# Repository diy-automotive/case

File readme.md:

# DIY automotive Project

ある日、普段からCHIRIMENを触っているおっさんとか、あまり触ってなかったおっさんなどが集まり、レーザービーム付き車載システムを手作りすることになった。

というわけで、ここでは手作りしたハードについて書く。
機能とかシステム構成とかについては、[システム構成とかの資料](https://github.com/diy-automotive/codes) を読んでください。

**1号機**    

## 前提

ハード構成は下記条件で検討した。

- 車載を想定したシステムであるが具体的な車種は規定しない。いまのところ。たぶんセダンタイプでも大丈夫な感じで作ろう。ということになった
- ダッシュボード上の空間に(取り外し可能な形で)設置。(ずっと置くと車検が通らないなど)。というわけで、全体で 奥行き30cm以内 x 幅15cm以内 x 高さ 10cm以内 程度の大きさの箱（ケース）に収める感じにする
- 本体はダッシュボード上に（仮止めとはいえ）固定するため、モニターはある程度角度調整が可能な構造とする
- タッチパネルで操作したい。モニタは5インチくらいの大きさが良いだろうということになった
- 電源はシガーソケット (DC 12V)から取る。ただし車載せずともデモができないとおもしろくないので、家庭用コンセント(AC 100V)とシガーソケット(DC 12V)を変換する電源ユニットもつくる
- GPSちゃんと取れるのか？怪しいが、一旦はフロントガラス経由でGPS測位できる想定で作る。(GPSモジュールを本体とは離して置けないと困るので本体からケーブルで伸ばせるようにする)
- スピーカーとマイクを近づけるとハウリングするのでスピーカーとマイクを離して設置できる構造が必要。マイクを離す手もあったけど、マイクはUSBカメラと一体になってるのを使いたかったので、スピーカーを外付けすることにした。

## パーツ一覧 

というわけで、冒頭の写真の「１号機」で使ったパーツは下記の通り。

### A. そのまま使うパーツ

1. [Raspberry Pi 3 Model B](https://www.raspberrypi.org/products/raspberry-pi-3-model-b/) x 1
2. [5インチ タッチパネルモニタ](https://www.amazon.co.jp/ELECROW-%E3%83%87%E3%82%A3%E3%82%B9%E3%83%97%E3%83%AC%E3%82%A4-800x480%E8%A7%A3%E5%83%8F%E5%BA%A6-%E3%82%BF%E3%83%83%E3%83%81%E3%82%B9%E3%82%AF%E3%83%AA%E3%83%BC%E3%83%B3-Raspberry/dp/B013JECYF2) x 1
3. [Raspberry Pi カメラモジュール v1.3 (車の前方撮影カメラ用)](http://akizukidenshi.com/catalog/g/gM-10476/)
4. [ポータブルスピーカ JVC SP-A35M-S](https://www.amazon.co.jp/gp/product/B002VITVE0/ref=oh_aui_detailpage_o02_s00?ie=UTF8&psc=1) x 1
5. [USB GPSモジュール GT-730F/L(SiRF)](http://akizukidenshi.com/catalog/g/gM-09272/) x 1
6. [Raspberry Pi カメラ用延長ケーブル (20cm〜)](https://www.amazon.co.jp/gp/product/B00KDZBCD6/ref=oh_aui_detailpage_o01_s00?ie=UTF8&psc=1) x 1
7. [HDMI延長アダプタ (L字 180度回転)](https://www.amazon.co.jp/gp/product/B0721MJGNN/ref=oh_aui_detailpage_o02_s00?ie=UTF8&psc=1) x 1
8. [スリムHDMIケーブル](https://www.amazon.co.jp/gp/product/B00KPP3MPA/ref=oh_aui_detailpage_o08_s00?ie=UTF8&psc=1) x 1 
9. [赤色ドットレーザー](http://akizukidenshi.com/catalog/g/gM-11821/)
10. [シガープラグ電源ケーブル](https://www.amazon.co.jp/gp/product/B01KRFE63Y/ref=oh_aui_detailpage_o01_s00?ie=UTF8&psc=1) x 1
11. [RCサーボ ブラケットセット](https://robot.tsukumo.co.jp/products/detail/644) x 2
12. [L字型 3.5mmステレオオーディオジャック延長ケーブル (10cmくらい)](https://www.aliexpress.com/item/DC3-5mm-Male-to-Female-Extension-stereo-Audio-Cable-15cm-90-Degree-Angled/32262817004.html?spm=a2g0s.9042311.0.0.ZXPDmG)
13. [USB延長ケーブル (Type A)]()
14. [12V 5A ACアダプタ](http://akizukidenshi.com/catalog/g/gM-06961/)
15. [シガーソケット電源ケーブル](https://www.amazon.co.jp/%E3%82%B7%E3%82%AC%E3%83%BC%E3%82%BD%E3%82%B1%E3%83%83%E3%83%88-%E3%83%A1%E3%82%B9-12V%E7%94%A8-%E9%9B%BB%E6%BA%90%E3%82%B1%E3%83%BC%E3%83%96%E3%83%AB%E4%BB%98-30cm/dp/B078WPZV7Q/ref=sr_1_31?s=automotive&ie=UTF8&qid=1521952190&sr=1-31&keywords=%E9%9B%BB%E6%BA%90+%E3%82%B7%E3%82%AC%E3%83%BC%E3%82%BD%E3%82%B1%E3%83%83%E3%83%88)

 (※ 12. 13. を併せた[この製品](
https://www.amazon.co.jp/auto-AC-DC%E5%A4%89%E6%8F%9B%E3%82%A2%E3%83%80%E3%83%97%E3%82%BF%E3%83%BC12V-%E9%9B%BB%E6%BA%90%E5%A4%89%E6%8F%9B%E3%82%A2%E3%83%80%E3%83%97%E3%82%BF%E3%83%BC-%E3%82%B7%E3%82%AC%E3%83%BC%E3%82%BD%E3%82%B1%E3%83%83%E3%83%88%E3%82%BF%E3%82%A4%E3%83%97-HLT-1200500C/dp/B07116WZHF/ref=sr_1_28?s=automotive&ie=UTF8&qid=1521952061&sr=1-28&keywords=%E9%9B%BB%E6%BA%90+%E3%82%B7%E3%82%AC%E3%83%BC%E3%82%BD%E3%82%B1%E3%83%83%E3%83%88)でも良さそうだけど試してない)

### B. 改造して使うパーツ

1. [USBカメラ (F2Fカメラ用) iBuffalo BSWHD06M](https://www.amazon.co.jp/gp/product/B00GZAF89W/ref=oh_aui_detailpage_o02_s01?ie=UTF8&psc=1) x 1
2. Micro B USB電源ケーブル
3. USB Type Aコネクタが付いた USB2.0ケーブル

### C. 電子部品

1. [DCDCコンバータ](http://akizukidenshi.com/catalog/g/gK-07728/) x 1
2. [トグルスイッチ]()
3. コンデンサ 1000uF(35V) x 1、220uF(16V) x 2
4. LED x 2
5. 抵抗 1kΩ x 1 2kΩ x 1
6. ユニバーサル基板 x 2
7. 電線(5Aくらい流しても大丈夫そうな太いやつや、普通のジャンパーケーブル適量)
8. [Molex 1.25mmピッチコンタクト](https://www.sengoku.co.jp/mod/sgk_cart/detail.php?code=EEHD-4B5Z) 使うの5本だけど圧着難しくてミスるので x 10
9. [Molex 1.25mmピッチコネクタのハウジング (5P)](https://www.marutsu.co.jp/pc/i/41986/) x 2 (使うの1つだけど予備入れて)
10. [ADT7410温度センサー](http://akizukidenshi.com/catalog/g/gM-06675/) x 1
11. [Raspi用長足ピンソケット (2列x20)](http://akizukidenshi.com/catalog/g/gC-10702/) x 1
12. 分割ピンヘッダ(2.54mmピッチ) 1x40 x 1
13. [PCA9685 IC単体](https://jp.rs-online.com/web/p/led-display-drivers/7275649/)
14. チップ抵抗 (0805) 220Ω x 2 、10kΩ x 1
15. チップコンデンサ (0805) 10uF x 1
16. ゴムブッシュ(3mm径くらいのやつ) x 2

### D. ケース用パーツ

1. [金具 19Ω314-3 黒](https://www.amazon.co.jp/%E3%83%8F%E3%82%A4%E3%83%AD%E3%82%B8%E3%83%83%E3%82%AF-19%E3%82%AA%E3%83%A1%E3%82%AC314-3-%E3%82%B8%E3%83%A7%E3%82%A4%E3%83%B3%E3%83%88-19%CE%A9314-3-%E9%BB%92/dp/B00C39XL7K) x 2
2. [金具 BS-558](https://store.shopping.yahoo.co.jp/cocoatta/4903757115583.html?sc_e=slga_pla)
3. [金具 6005](https://store.shopping.yahoo.co.jp/ayahadio/4905034060050.html?sc_e=slga_pla)
4. [金具 6001](https://store.shopping.yahoo.co.jp/hands-net/4905034060012.html?sc_i=shp_pc_search_itemlist_shsr_title)

5. [アクリル版 (リンクにおいてあるdxfファイルでレーザーカットを依頼する)](https://github.com/diy-automotive/case)

### E. その他 (T.B.D.)

下記概要だけ記載しておく。※あとで詳細化する予定。

1. ネジ、スペーサー、ナット、ワッシャー等 (M2,M2.6,M3,M4) 適量
2. ジャンパーケーブル 適量
3. 電線適量。電源とかの工作に使う

## 制作に必要な工具

- 電動ドリル
- ドライバー
- はんだごて、はんだ吸い取り線、はんだ
- フラックス、フラックスクリーナー
- ラジオペンチ
- ニッパー
- カッター
- 圧着工具 ([PA-09](https://www.yodobashi.com/product/100000001002004022/)/[PA-20](https://www.yodobashi.com/product/100000001002493185/?gad1=&gad2=g&gad3=&gad4=56278881131&gad5=4733500117604394886&gad6=1o1&gclid=CjwKCAjw7tfVBRB0EiwAiSYGM2PXHVkw076M0nHblvUYxSvrJmiqklgOjumo8atqDQbhuTxs9HHcMBoCniEQAvD_BwE&xfr=pla))
- ワイヤーストリッパー

## 制作手順 

(T.B.D.) 写真いれる予定。。。

### 1. [アクリル板データ](./case/)のレーザーカットと修正

レーザーカットサービスにカットを依頼しておく。
リードタイムがかかるので、最低2週間前にはやっておく。
今回は、[elecrow Acrylic Laser Cutting Service](https://www.elecrow.com/5pcs-acrylic-laser-cutting-service.html)へ依頼。OCS使って1週間で届いた。

レーザーカットデータは残念ながら現時点(v1/v2両方) では不完全なので、`bottom.dxf`の1枚だけ（上部に利用する側のみ）ドリルで穴をあけておく。
 (将来v3以降で修正されるはずなので、この工程はなくなる予定) ※割れないよう慎重に行うこと

穴をあける箇所は特に指定はないが、下記 2箇所 (穴としては5穴) の穴あけを行う。

- トグルスイッチ固定用の穴 (6mmくらいの穴をあける。いきなりこれを開けようとすると割れるので2mmくらいの穴を広げた方が良い)
- サーボモータ固定用の穴 (サーボモータ固定用の穴はすでに空いているが、後ろ側に寄りすぎていて干渉するため、同じような 4隅 9mm 間隔 2mmの穴を　よりケースの端側に開ける )

### 2. [HAT](./hat/)の基板を製造

基板製造業者に投げておく。回しものではないが [elecrow](https://www.elecrow.com/pcb-manufacturing.html) にアクリル板と一緒に投げると一緒に送ってくれる。

### 3. 電源ユニットの制作

電源ユニットは、下記で構成される。AC電源側から記載する

1. ACアダプタ (加工の必要なし)
2. シガーソケット (電線の端にDCジャックを付けておく) ※基板で加工が必要
3. シガープラグ (電線の端をDCDCコンバータの入力側に接続。ターミナル経由なのでネジ止めだけ)
4. DCDCコンバータ (秋月のキットなので、そのまま作ればOK)
5. 分岐基板 (DCDCの出力側のターミナルにつなぐケーブルの先を2列のピンヘッダで分岐させる用の基板。DCDCの出力側のVCCラインにトグルスイッチを付けておく)

上記分岐基板につなぐのは、Raspiの電源と、サーボモータの電源だが両方ケーブルの改造が必要となる。

#### 3.1 Raspi電源用ケーブルの改造

市販のmicro B端子の付いたUSB充電ケーブルを切断、USB micro Bコネクタ側を残して切断した側をQIコネクタ(メス)に加工する

#### サーボモータの電源

これはHATの項に記載。

### 4. HATの制作とRaspiとの固定

[HAT](./hat/)のデータは今回用に設計したものではないので、いろいろそのままは使わない。
PCA9685関連の部分のみ作る感じで PCA9685と周辺のチップコンデンサ(10uF)、チップ抵抗(220Ω x 2, 10kΩ x 1)、サーボ接続用のピンヘッダ、RaspiのGPIO接続用の長足ピンソケットだけハンダ付け。電源はUSB経由ではなく表面のRaspiの電源付近にあるコンデンサ(220uF)の部分にコンデンサと一緒にケーブル（太めを付けないと燃える。燃えた）を直接はんだ付けし、ケーブル反対側を電源ユニットのジャンパーに刺せるようQIコネクタ（メス）に加工しておく。ケーブルの長さは10cm程度で良い。

HATが制作できたら、Raspiに固定する。
まず、Raspiにある4箇所の固定用穴の底面にM2.6mmのスペーサー（片方がネジになってる。ネジ側をRaspiの穴に挿す）と、上面に、両方がナットになってるスペーサーで挟み込んで止める。これを4箇所ともやっておく。

次に、HATをRaspiに重ね、HATの上からM2.6のネジで、下のスペーサーとHATを挟み込むような形でネジ止めしておく。

### 5. P2P通話用カメラの改造

USBカメラを分解し、基板部分のみ利用する。
基板の1.25mmピッチコネクタと反対側がUSB Type Aになったケーブルを別途制作する。安いUSBケーブルを切って端子を圧着して作る。
1.25mmピッチコネクタの圧着が難しいので注意。圧着工具PA-09を使う。

### 6. 前景撮影用カメラユニットの作成

サーボで動くカメラユニットを作成する。

`camera-parts-v2.dxf`を出力したアクリル板を使いRaspiカメラと小型レーザーを組み合わせたユニットを作る。
M2のスペーサーとネジを使って固定するが、`camera-parts-v2.dxf`の後面側のパーツは穴の間隔が合わないので、下の穴はスペーサーで終端にする。
レーザーはゴムブッシュでアクリル板に固定する。

次に、サーボブラケットセットを組み立てる。カメラとレーザーを組み合わせたユニットを最後にネジ止めする

カメラのリボンケーブルは、一番下側になるサーボブラケットの中を通すようにしておくとあとあと取り回しがしやすい。

### 7. モニター部分の制作

モニターとP2P通話用カメラをアクリルケースに固定する。
`back.dxf`を出力したアクリル板と、`front.dxf`を出力したアクリル板を使う。

1. M2のネジ・スペーサを使ってカメラを`front.dxf`を出力したアクリル板へ固定する

2. `back.dxf`を出力したアクリル板へ、[金具 6001](https://store.shopping.yahoo.co.jp/hands-net/4905034060012.html?sc_i=shp_pc_search_itemlist_shsr_title) をネジ止めする。モニターとの隙間に干渉しないよう、6mmくらいのネジ推奨。

3. モニターの背面に4箇所 M2のネジが出ているので、そこにM2のスペーサー (5mm) を4箇所止める。
4. `back.dxf`を出力したアクリル板とスペーサーをM2ネジで固定する。
5. 最後にカメラを固定した`front.dxf`を出力したアクリル板と、`back.dxf`を出力したアクリル板を M2 13mmのスペーサー経由でネジ止めして固定する

### 8. 本体部分の制作(底面から)

`bottom.dxf` 2枚で本体ケース部分を作る。2枚のうち1枚は、1. の工程で穴あけ加工済み。こちらは上面に使うので、ここでは加工していないもう１枚を使う。

1. アクリル板に、足となる [金具 19Ω314-3](https://www.amazon.co.jp/%E3%83%8F%E3%82%A4%E3%83%AD%E3%82%B8%E3%83%83%E3%82%AF-19%E3%82%AA%E3%83%A1%E3%82%AC314-3-%E3%82%B8%E3%83%A7%E3%82%A4%E3%83%B3%E3%83%88-19%CE%A9314-3-%E9%BB%92/dp/B00C39XL7K) のうち、Raspiの電源側に近い部分の方を先にネジ止めしておく。M4ネジを使い、アクリル板との間にはゴムワッシャーを入れておく。(振動対策)Raspiを重ねた後でネジが入れられなくなるため。あとで手で絞められるように蝶ナットを使う。
2. アクリル板に、4. でHATをつなげたRaspiをネジ止めする。Raspi側の底面にスペーサーが付いているので、アクリル板の反対側からネジ止めするだけで固定できるが、Raspiの電源側の角のネジだけは止めないでおく。下の足と干渉するため。
3. 次に電源ユニットをネジ止めする。間にスペーサーを入れた方がやりやすそうだがお好みで。
4. 5cmの M3スペーサーを、アクリル板の4角に付けておく。このスペーサーで上面との固定を行う。
5. 反対側の足(金具 19Ω314-3)もつけておく。こちら側もゴムワッシャー経由でアクリル版とネジで固定するが、(金具 19Ω314-3)の下に[金具 BS-558](https://store.shopping.yahoo.co.jp/cocoatta/4903757115583.html?sc_e=slga_pla) を挟んでから止めておく。金具 BS-558は、のちにモニターとの接続に使う。

### 9. 本体部分の制作(上面)

`bottom.dxf` 1. の工程で穴あけ加工済みの方のアクリル版を使い上面パネルを作る。
このパネルには、電源ユニットのトグルスイッチと、 前景撮影用カメラユニット(サーボモータブラケット) を接続する

1. トグルスイッチは穴にトグルスイッチを通して、付属のワッシャーで固定する。
2. カメラユニットのサーボブラケットは、モーターの停止位置を調整したうえで、サーボホーンもネジ止めし（とても重要！モーターを壊す原因に！）アクリル版にM2ネジとナットで固定する

### 10. 配線と 本体部分の接続 (側面パネル、スペーサー経由で固定)

底面と上面を接続する前に、8. の底面パネル面で配線を行なっておく。

1. サーボモーターのコードは上パネルの丸い大きな穴経由でHATのピンヘッダに接続 (2つとも)
2. カメラはリボンケーブルを同様に上パネルの丸い大きな穴経由でRasoiのカメラコネクタに接続(HATが邪魔でやりにくいのでラジオペンチ等を使う)
3. マウス+キーボード用のUSBドングルをRaspiのUSBポートに挿しておく
4. 延長ケーブル経由でGPSレシーバもUSBポートに挿しておき、前景側の開口部から出しておく
5. L字オーディオジャックを挿して、これも前景側の開口部から出しておく
6. HDMIケーブルはケースの中に収まるよう丸めながらRaspiのHDMIコネクタに挿し、モニタ側の開口部に反対側を出しておく
7. 電源ユニットの電源ケーブルもモニタ側の開口部から出しておく
8. モニタの電源、タッチパネル用のジャンパーケーブルをRaspiのGPIOに挿し、反対(オス)側をモニタ側に出しておく

上記配線後、`front.dxf` (v2の場合は `camera-parts-v2.dxf` に含まれる) に含まれる側面用のパーツを底面パネルの穴に垂直に挿しこみ、最後に 9. で制作した上面パネルを底面に設置済みの5cmスペーサーとの間のネジ止めにより固定する。

### 11. 本体とモニター部分の固定

1. モニターに付属の「コ」の字型のHDMIコネクタと別途用意したL字型コネクタをモニター部分に接続し、そこに本体から出ているHDMIケーブルを接続する
2. 本体側から出ているジャンパーケーブルをモニタに接続する (VCC,GND,SPI)
3. P2P用カメラのUSBケーブルを接続する

上記接続が終わったら、最後に [金具 6005] を使い、モニタ側の[金具 6001]と、本体側の[金具 BS-558]をネジ止めしてモニタの「首」の部分を作って完成！

## 課題

いくつか既知の課題があるので、issueに登録することにする。

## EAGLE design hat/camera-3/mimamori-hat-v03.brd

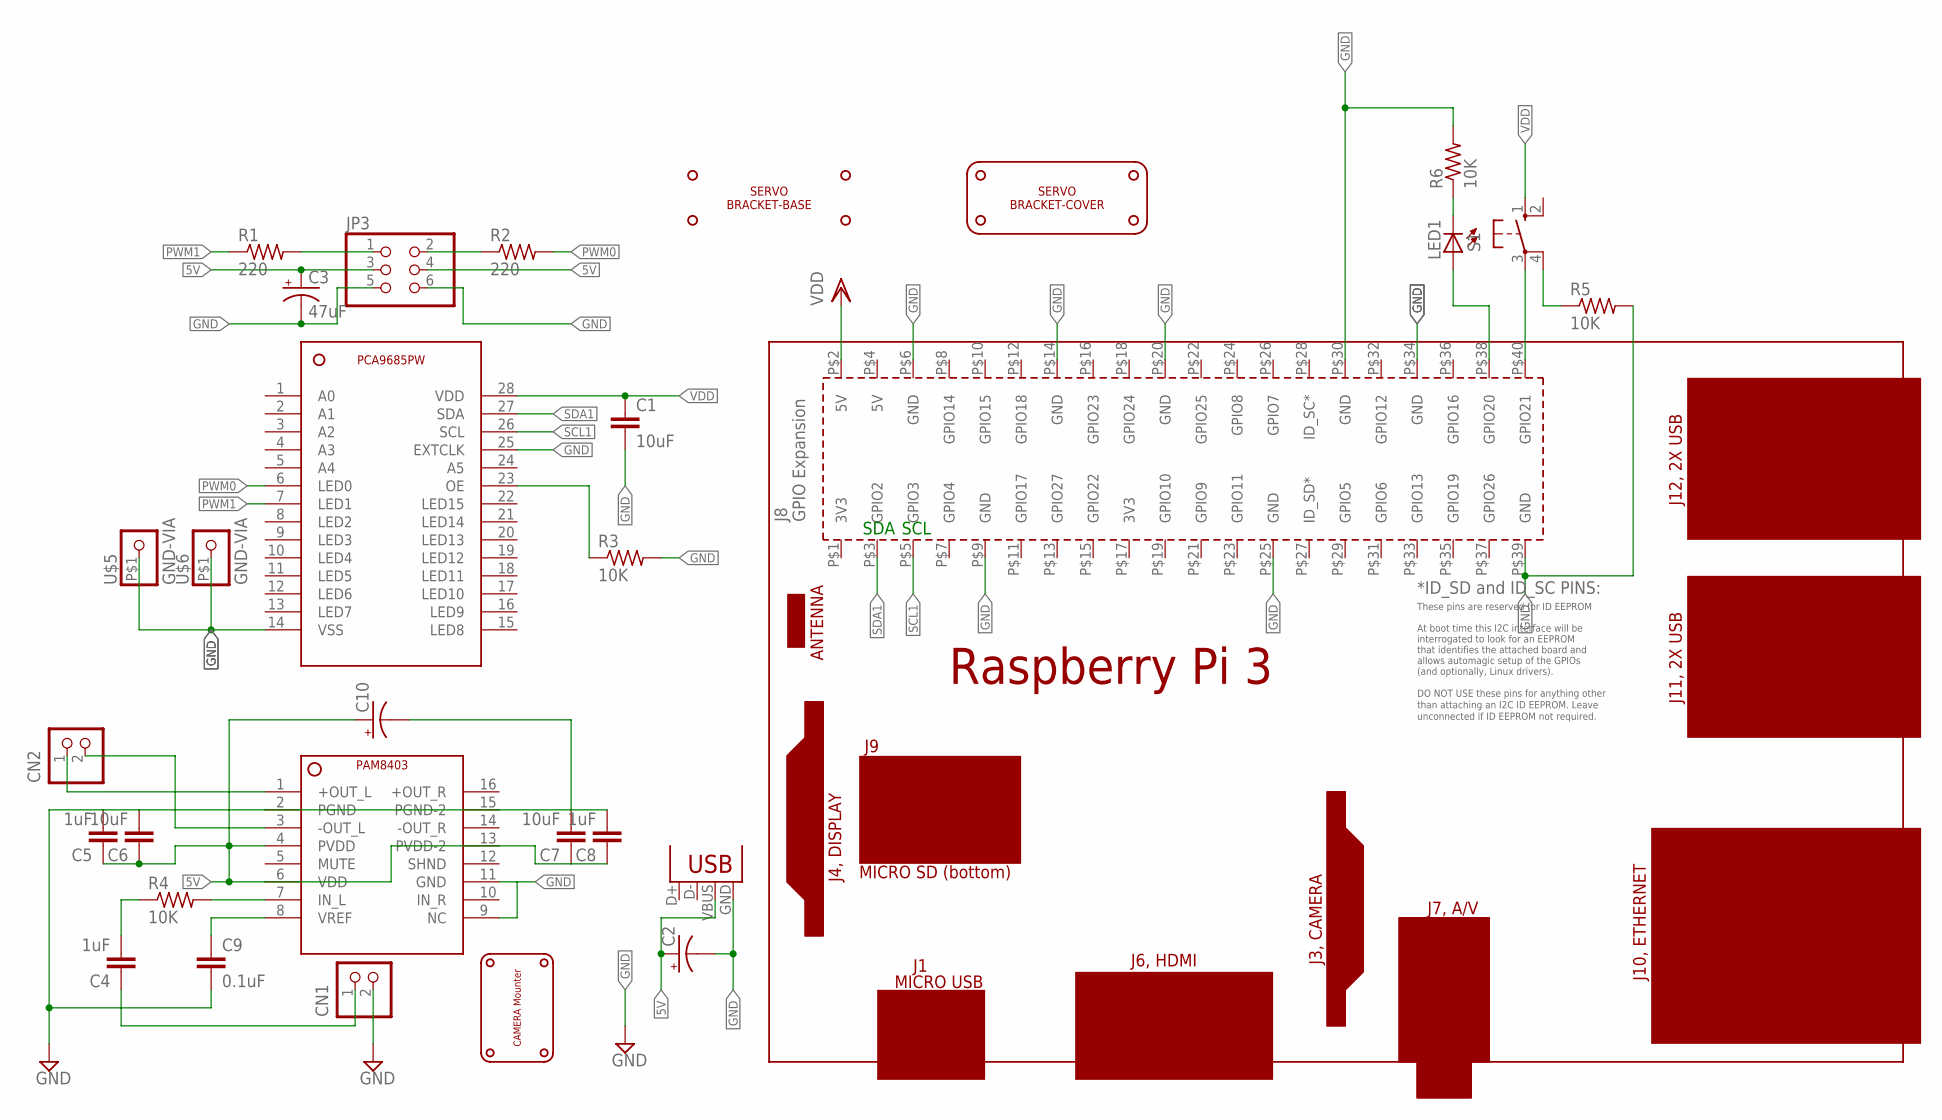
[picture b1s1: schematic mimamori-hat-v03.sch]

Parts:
C1, C6, C7: 10uF; C0805
C2, C10: CPOL-US153CLV-0810; 153CLV-0810
C3: 47uF; 153CLV-0605
C4, C5, C8: 1uF; C0805
C9: 0.1uF; C0805
CN1, CN2: B2B-PH-K-S
JP1: USB-MICROB
JP3: PINHD-2X3; 2X03
LED1: LED3MM
PCB1: RPI3
R1, R2: 220; R0805
R3, R4, R5, R6: 10K; R0805
S1: 10-XX; B3F-10XX
U$1: PAM8403; SOP16
U$2: PCA9685PW; TSSOP28
U$3: CAMERA-MOUNTER
U$4: SERVO-BRACKET-BASE; SERVO-BRACKET
U$5, U$6: GND-VIA
U$7: SERVO-BRACKER-COVER; SERVO-BRACKET-COVER

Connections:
5V: C2.+, C3.+, C5.1, C6.1, C7.1, C8.1, C10.+, JP1.VBUS, JP3.3, JP3.4, U$1.4 (PVDD), U$1.6 (VDD), U$1.13 (PVDD-2)
GND: C1.2, C2.-, C3.-, C5.2, C6.2, C7.2, C8.2, C9.2, C10.-, CN1.2, JP1.GND, JP3.5, JP3.6, PCB1.P$6 (GND), PCB1.P$9 (GND), PCB1.P$14 (GND), PCB1.P$20 (GND), PCB1.P$25 (GND), PCB1.P$30 (GND), PCB1.P$34 (GND), PCB1.P$39 (GND), R3.2, R5.2, R6.2, U$1.2 (PGND), U$1.9 (NC), U$1.11 (GND), U$1.15 (PGND-2), U$2.14 (VSS), U$2.25 (EXTCLK), U$5.P$1, U$6.P$1
unnamed: JP3.1, R1.2
unnamed: JP3.2, R2.1
unnamed: R3.1, U$2.23 (OE)
unnamed: C4.1, CN1.1
unnamed: C4.2, R4.1
unnamed: R4.2, U$1.7 (IN_L)
unnamed: C9.1, U$1.8 (VREF)
unnamed: CN2.1, U$1.1 (+OUT_L)
unnamed: CN2.2, U$1.3 (-OUT_L)
unnamed: R5.1, S1.4 (P1)
unnamed: PCB1.P$40 (GPIO21), S1.3
unnamed: LED1.A, PCB1.P$38 (GPIO20)
unnamed: LED1.K (C), R6.1
PWM0: R2.2, U$2.6 (LED0)
PWM1: R1.1, U$2.7 (LED1)
SCL1: PCB1.P$5 (GPIO3), U$2.26 (SCL)
SDA1: PCB1.P$3 (GPIO2), U$2.27 (SDA)
VDD: C1.1, PCB1.P$2 (5V), S1.1 (S), U$2.28 (VDD)

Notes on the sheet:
SDA
SCL

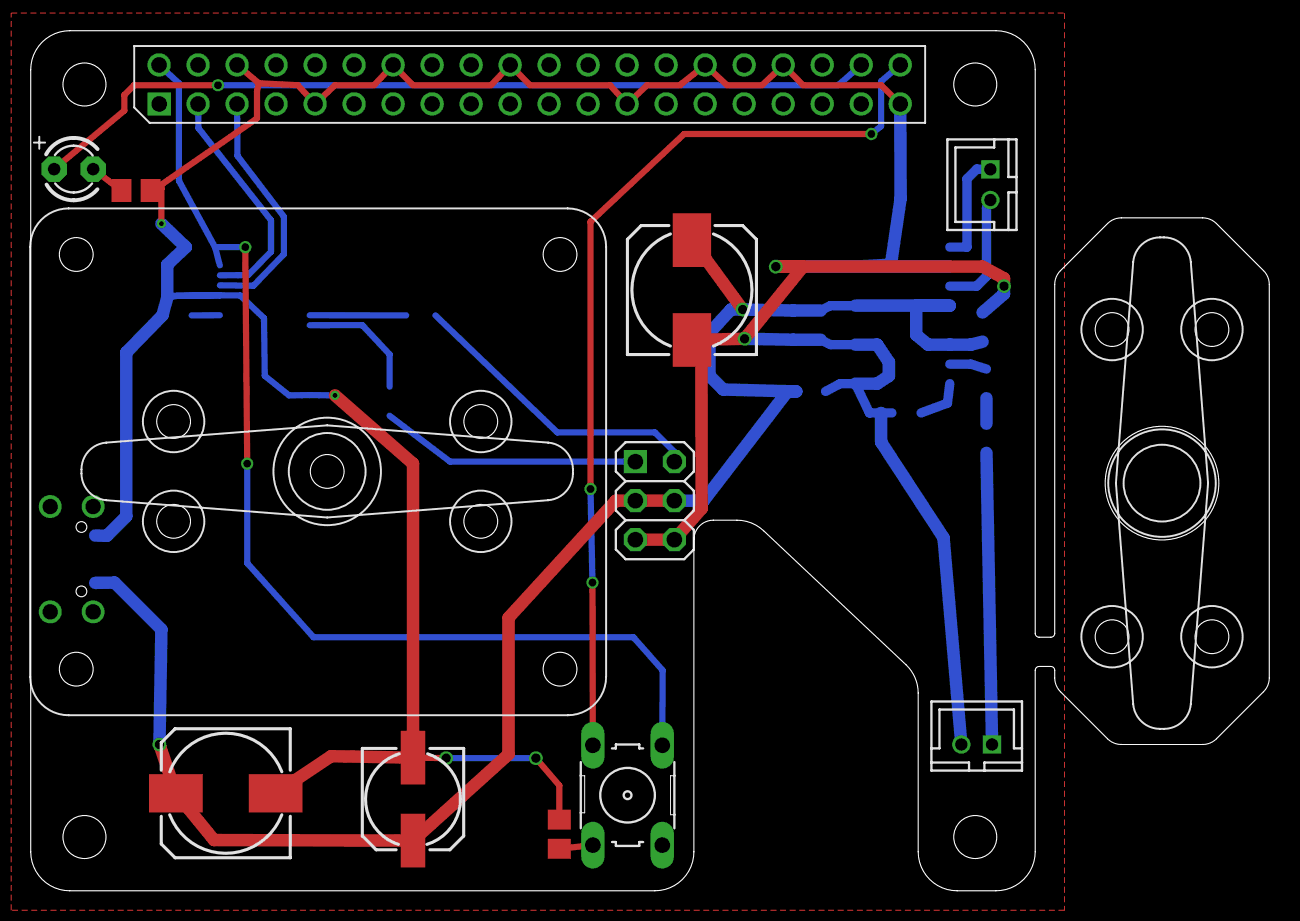
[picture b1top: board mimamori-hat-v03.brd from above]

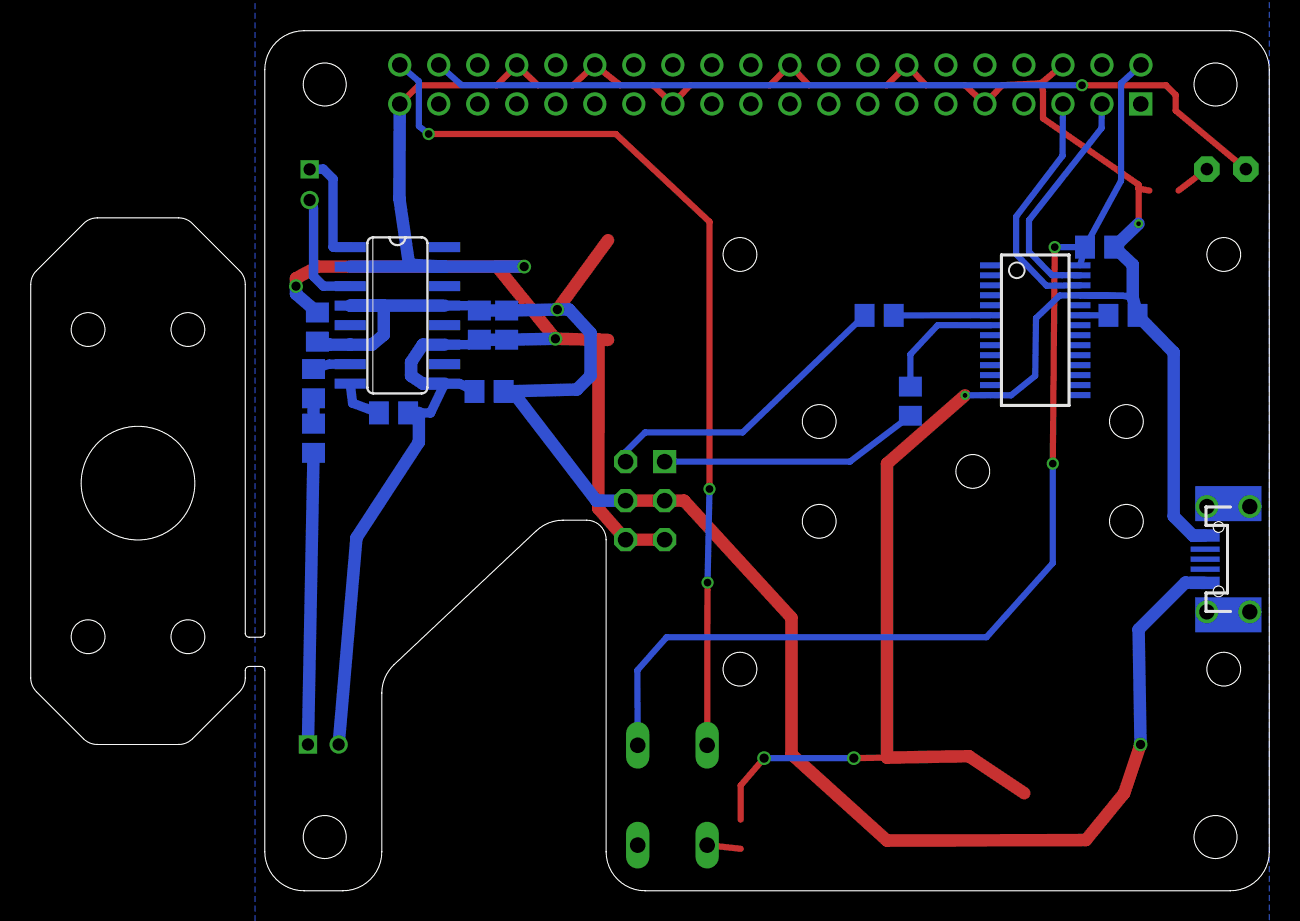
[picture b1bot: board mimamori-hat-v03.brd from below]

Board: 2 copper layers, 80.6 x 56.0 mm, 30 parts (14 on the bottom side), 20 nets.

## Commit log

2018-03-25 add eagle files (v1/v2)
2018-03-25 rename
2018-03-25 add readme.md, hat, lbr
2018-03-25 fix link in readme.md
